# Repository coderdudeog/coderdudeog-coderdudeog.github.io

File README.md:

My project is a rocket flight controller board I designed in KiCad. It uses an STM32F103 MCU, a BMP280 barometer, and an ICM2060 ICM. It has a
microSD card slot to store data collected from the sensors. It runs on 3.3v gathered from a single cell LiPo battery. There's a power 
regulation system built into the DAC on PA0. That's about it.

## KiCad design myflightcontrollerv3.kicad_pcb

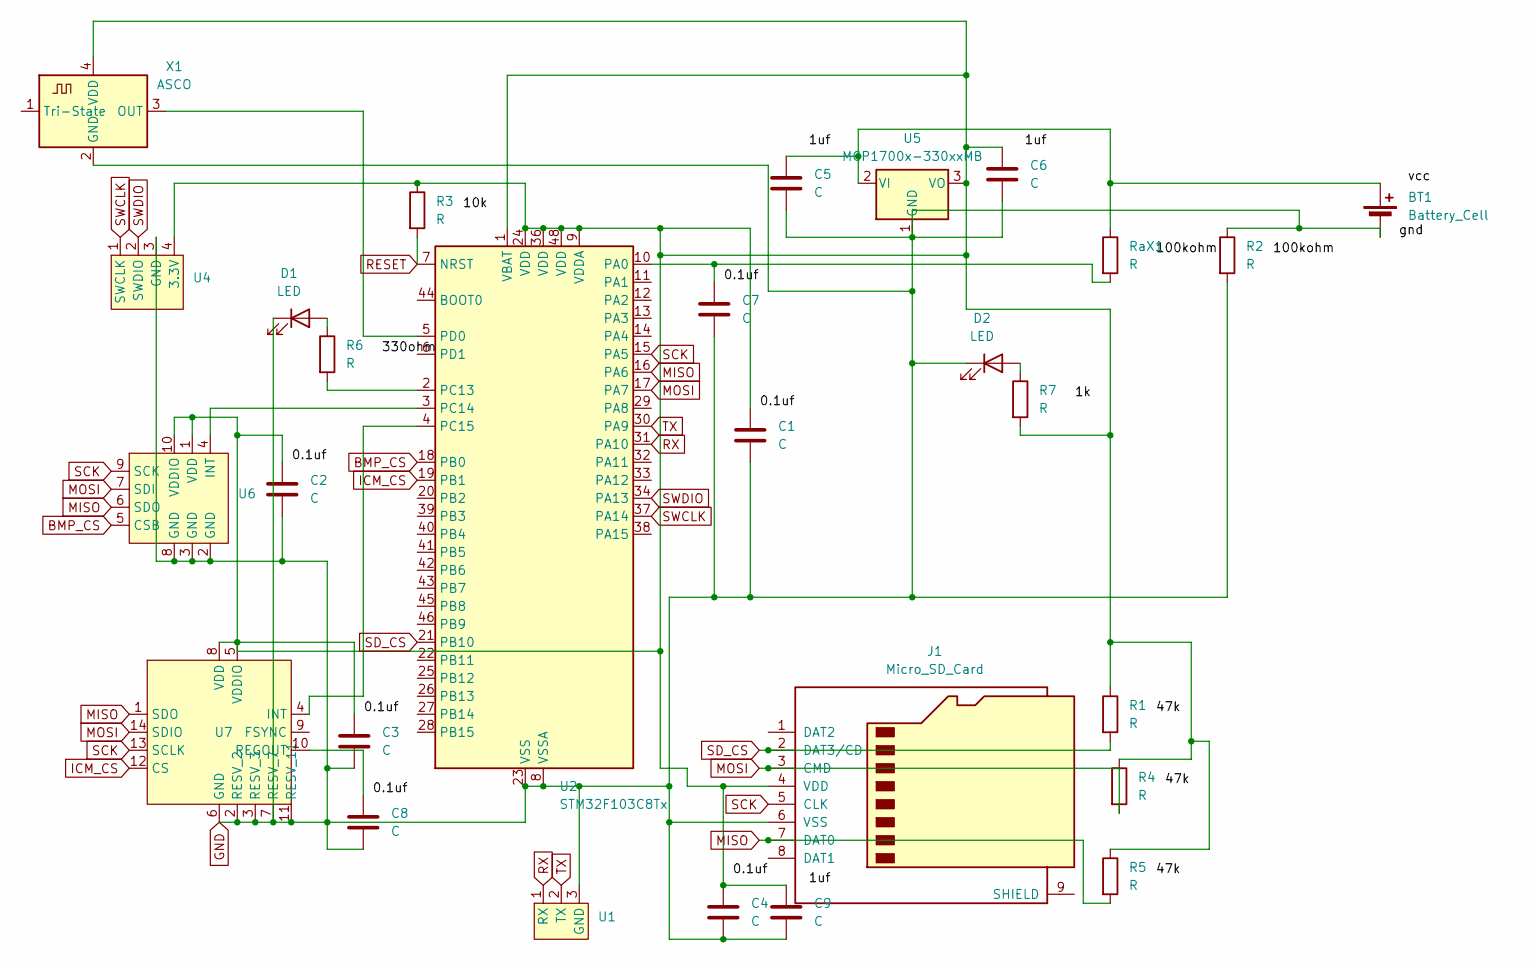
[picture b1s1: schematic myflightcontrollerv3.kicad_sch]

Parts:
BT1: Battery_Cell; JST_PH_B2B-PH-K_1x02_P2.00mm_Vertical
C1, C2, C3, C4, C5, C6, C7, C8, C9: C; C_0805_2012Metric_Pad1.18x1.45mm_HandSolder
D1, D2: LED; LED_0603_1608Metric
J1: Micro_SD_Card; microSD_HC_Molex_104031-0811
R1, R2, R3, R4, R5, R6, R7: R; R_0805_2012Metric
RaX1: R; R_0805_2012Metric
U1: PinSocket_1x03_P2.54mm_Vertical
U2: STM32F103C8Tx; LQFP-48_7x7mm_P0.5mm
U4: PinHeader_1x04_P2.54mm_Vertical
U5: MCP1700x-330xxMB; SOT-89-3
U6: Rohm_MLGA010V020A_LGA-10_2x2mm_P0.45mm_LayoutBorder2x3y
U7: LGA-14_3x2.5mm_P0.5mm_LayoutBorder3x4y
X1: ASCO; Oscillator_SMD_EuroQuartz_XO53-4Pin_5.0x3.2mm

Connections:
BMP_CS: U2.18 (PB0), U6.5 (CSB)
GND: BT1.2 (-), C1.2, C2.2, C3.2, C4.2, C5.2, C6.2, C7.2, C8.2, C9.2, D1.1 (K), D2.1 (K), J1.6 (VSS), R2.1, R2.2, U1.3 (GND), U2.8 (VSSA), U2.23 (VSS), U2.35 (VSS), U2.47 (VSS), U4.3 (GND), U5.1 (GND), U6.2 (GND), U6.3 (GND), U6.8 (GND), U7.2 (RESV_2), U7.3 (RESV_3), U7.6 (GND), U7.7 (RESV_7), U7.11 (RESV_11), X1.2 (GND)
ICM_CS: U2.19 (PB1), U7.12 (CS)
MISO: J1.7 (DAT0), R5.2, U2.16 (PA6), U6.6 (SDO), U7.1 (SDO)
MOSI: J1.3 (CMD), R4.2, U2.17 (PA7), U6.7 (SDI), U7.14 (SDIO)
unnamed: BT1.1 (+), C5.1, RaX1.1, U5.2 (VI)
unnamed: D1.2 (A), R6.1
unnamed: D2.2 (A), R7.1
unnamed: C1.1, C2.1, C3.1, C4.1, C6.1, C9.1, J1.4 (VDD), R1.1, R3.1, R4.1, R5.1, R7.2, U2.1 (VBAT), U2.9 (VDDA), U2.24 (VDD), U2.36 (VDD), U2.48 (VDD), U4.4 (3.3V), U5.3 (VO), U6.1 (VDD), U6.10 (VDDIO), U7.5 (VDDIO), U7.8 (VDD), X1.4 (VDD)
unnamed: C7.1, RaX1.2, U2.10 (PA0)
unnamed: R6.2, U2.2 (PC13)
unnamed: U2.3 (PC14), U6.4 (INT)
unnamed: U2.4 (PC15), U7.4 (INT)
unnamed: U2.5 (PD0), X1.3 (OUT)
unnamed: C8.1, U7.10 (REGOUT)
RESET: R3.2, U2.7 (NRST)
RX: U1.1 (RX), U2.31 (PA10)
SCK: J1.5 (CLK), U2.15 (PA5), U6.9 (SCK), U7.13 (SCLK)
SD_CS: J1.2 (DAT3/CD), R1.2, U2.21 (PB10)
SWCLK: U2.37 (PA14), U4.1 (SWCLK)
SWDIO: U2.34 (PA13), U4.2 (SWDIO)
TX: U1.2 (TX), U2.30 (PA9)

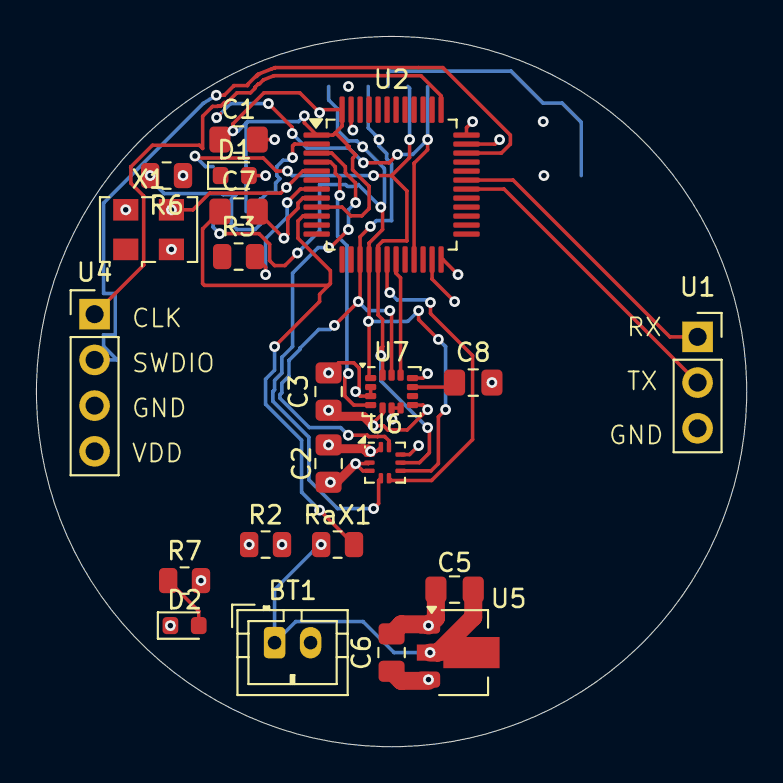
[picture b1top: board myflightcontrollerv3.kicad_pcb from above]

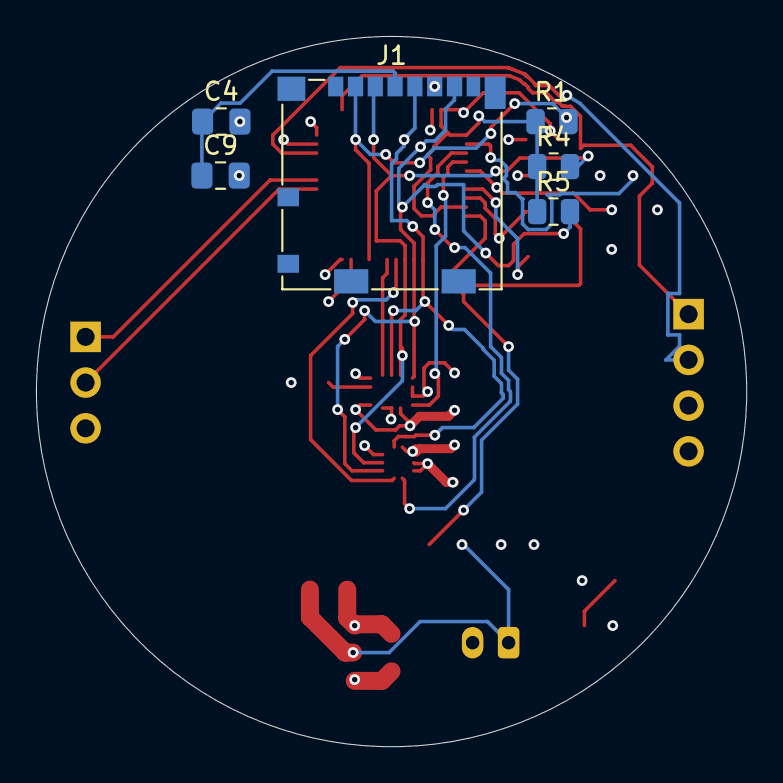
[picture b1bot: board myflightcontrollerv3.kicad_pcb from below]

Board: 4 copper layers, 39.5 x 39.5 mm, 28 parts (6 on the bottom side), 22 nets.

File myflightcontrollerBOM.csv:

Comment,Designator,Footprint
0.1uF,C1 C2 C3 C4 C7 C8,Capacitor_SMD:C_0201_0603Metric
1uF,C5 C6 C9,
LED,"D1,D2",LED_SMD:LED_0201_0603Metric
Micro_SD_Card,J1,Connector_Card:microSD_HC_Molex_104031-0811
100k,RaX1 R2,Resistor_SMD:R_0201_0603Metric
10k,R3,
47k,R1 R4 R5,
330ohm,R6,
1k,R7,
BMP280,U1,Package_LGA:Bosch_LGA-8_2x2.5mm_P0.65mm_ClockwisePinNumbering
STM32F103C8Tx,U2,Package_QFP:LQFP-48_7x7mm_P0.5mm
ICM-20602,U3,Package_LGA:LGA-16_3x3mm_P0.5mm_LayoutBorder3x5y
MCP1700x-330xxMB,U5,Package_TO_SOT_SMD:SOT-89-3
